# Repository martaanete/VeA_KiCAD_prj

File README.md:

# VeA_KiCAD_prj
//projekts kursa darbs.

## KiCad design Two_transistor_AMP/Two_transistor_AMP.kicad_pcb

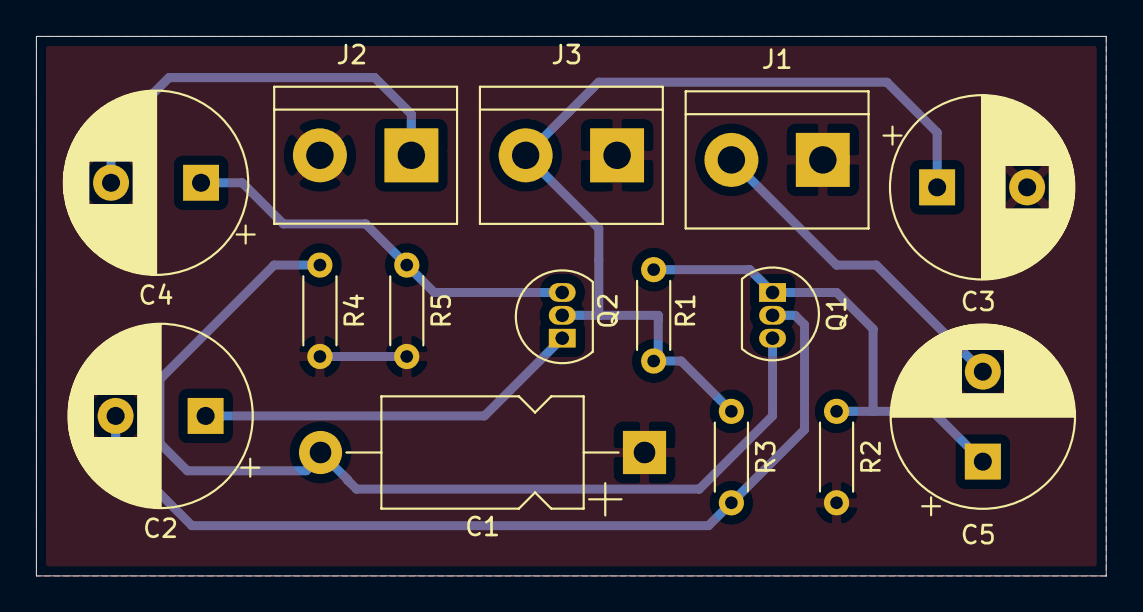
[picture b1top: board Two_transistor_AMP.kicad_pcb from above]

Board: 2 copper layers, 59.4 x 30.0 mm, 15 parts (0 on the bottom side), 9 nets.

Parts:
C1: 4.7uF; CP_Axial_L11.0mm_D6.0mm_P18.00mm_Horizontal
C2, C5: 0.47uF; CP_Radial_D10.0mm_P5.00mm
C3: 47uF; CP_Radial_D10.0mm_P5.00mm
C4: 33uF; CP_Radial_D10.0mm_P5.00mm
J1, J2: Conn_01x02; TerminalBlock_bornier-2_P5.08mm
J3: 9V; TerminalBlock_bornier-2_P5.08mm
Q1, Q2: Q_NPN_BCE; TO-92L_Inline
R1: 220k; R_Axial_DIN0204_L3.6mm_D1.6mm_P5.08mm_Horizontal
R2: 27k; R_Axial_DIN0204_L3.6mm_D1.6mm_P5.08mm_Horizontal
R3, R5: 10k; R_Axial_DIN0204_L3.6mm_D1.6mm_P5.08mm_Horizontal
R4: 1.5k; R_Axial_DIN0204_L3.6mm_D1.6mm_P5.08mm_Horizontal

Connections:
GND: C1.1, C3.2, J1.1, J2.2, J3.1, R2.2, R4.2, R5.2
unnamed: C1.2, Q1.3, R4.1
unnamed: C2.1, Q2.1
unnamed: C2.2, Q1.2, R3.2
unnamed: C3.1, J3.2, Q2.2, R1.1, R3.1
unnamed: C4.1, Q2.3, R5.1
unnamed: C4.2, J2.1
unnamed: C5.1, Q1.1, R1.2, R2.1
unnamed: C5.2, J1.2

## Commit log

2021-10-05 README update to test GitHub Repo
2021-11-01 Majasdarbs
